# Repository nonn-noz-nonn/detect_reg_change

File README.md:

# 変動する抵抗値の観測

## 概要

- 対象のArduino : Arduino Uno Rev3
- 対象の抵抗値 : 0ohm - 500kohm
    - 電圧変換した抵抗値を0-1023 (10bit) の値として取得します．
- kohmオーダの抵抗値であれば±20dB程度の変動は取得できます．
    - ※ 取得した値の絶対値と精度は考慮していません．
- 下記の項目をシリアルターミナル上で設定できます．
    - 取得する値の下限
    - 取得する値の上限
    - LED点灯の閾値
    - LED点灯の論理
    - 1次LPFの係数
    - 取得間隔(目安)

※ 設定値の範囲や設定方法はArduinoスケッチをご覧ください．

## ソフトウェアのバージョン

作成に用いたソフトウェアのバージョンは次の通りです．

| ソフト名 | バージョン |
| ---- | ---- |
| Arduino IDE | 1.8.19 |
| KiCad | 6.0.2 |

## 注意

本リポジトリのコンテンツ (回路図，BOM，KiCad関連ファイル，Arduinoスケッチ) を流用，応用することは自由ですが，流用・応用した結果生じた問題・障害・損害について，作者 (nonn_noz_nonn (nonn-noz-nonn) ) は一切の責任を負いません．

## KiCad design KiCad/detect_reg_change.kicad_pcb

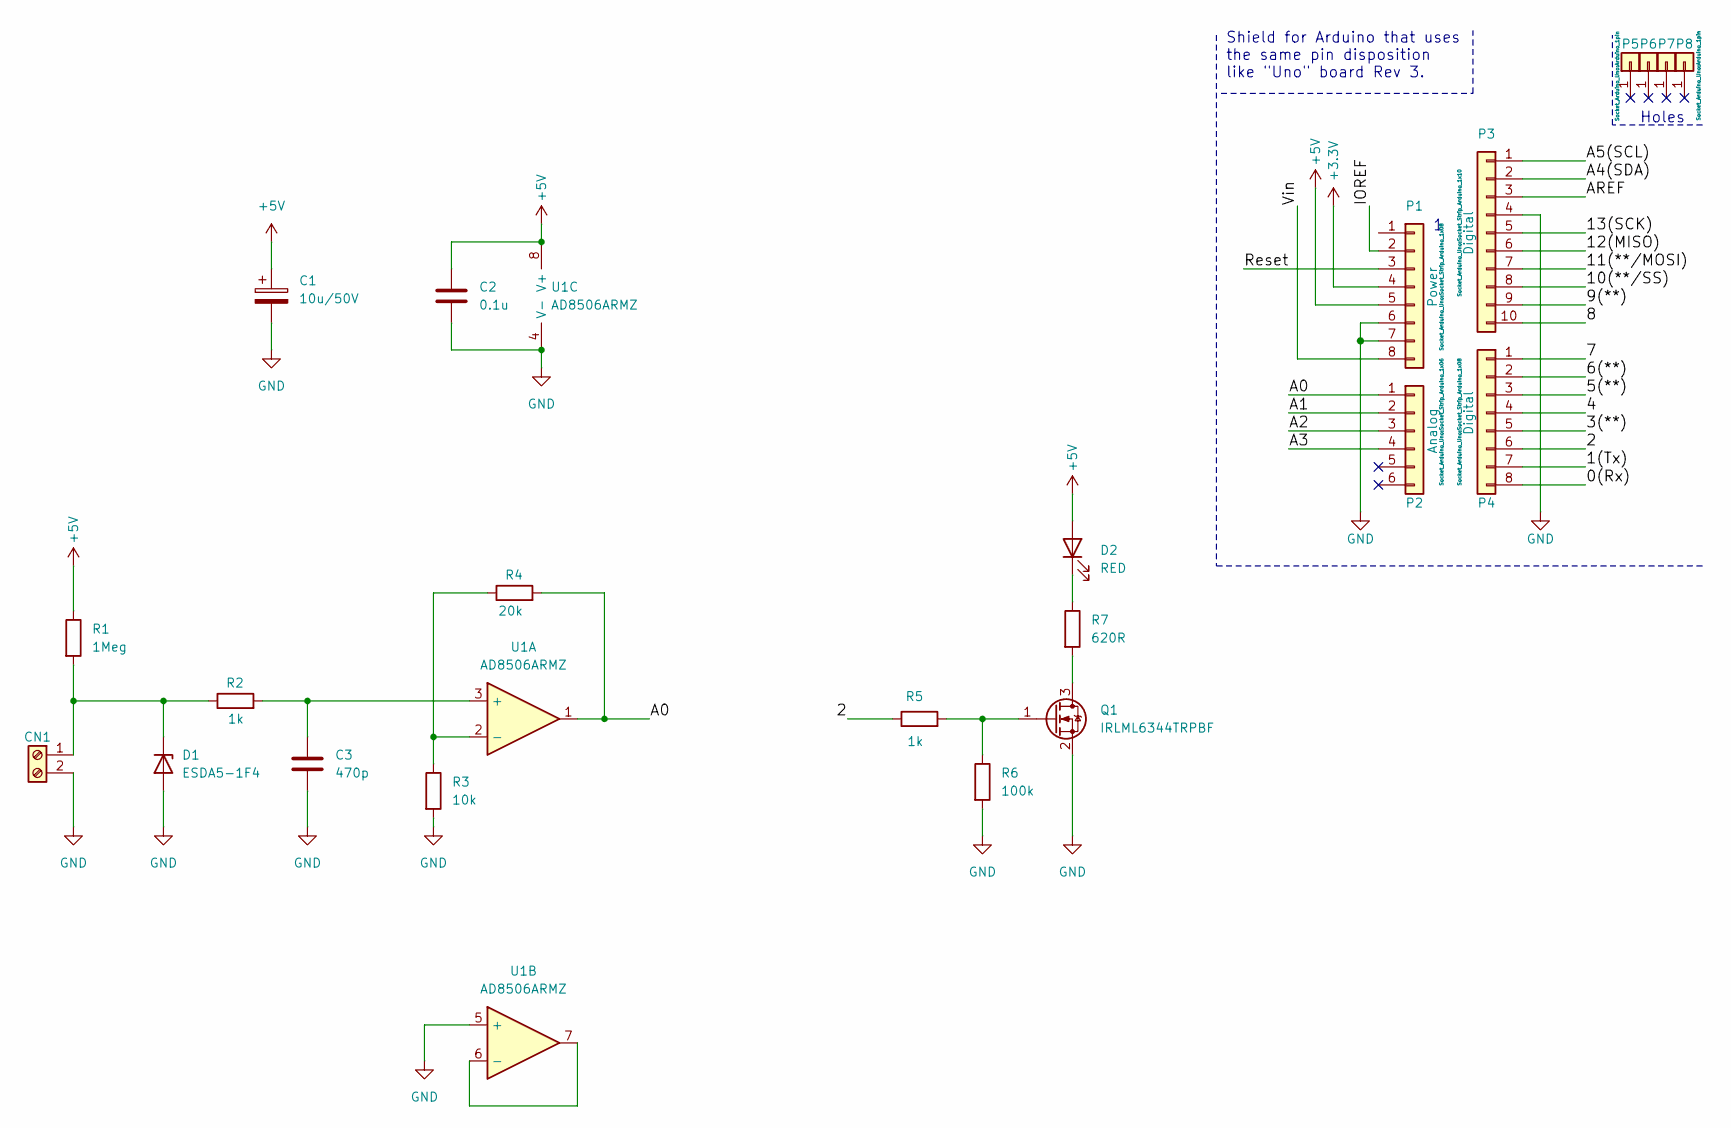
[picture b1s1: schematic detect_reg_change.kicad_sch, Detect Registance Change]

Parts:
C1: 10u/50V; CP_Elec_5x5.4
C2: 0.1u; C_0603_1608Metric
C3: 470p; C_0603_1608Metric
CN1: Screw_Terminal_01x02; PinSocket_1x02_P2.54mm_Vertical
D1: ESDA5-1F4; D_0201_0603Metric
D2: RED; LED_0603_1608Metric
P1: Power; Socket_Strip_Arduino_1x08
P2: Analog; Socket_Strip_Arduino_1x06
P3: Digital; Socket_Strip_Arduino_1x10
P4: Digital; Socket_Strip_Arduino_1x08
P5, P6, P7, P8: CONN_01X01; Arduino_1pin
Q1: IRLML6344TRPBF; SOT-23
R1: 1Meg; R_0603_1608Metric
R2, R5: 1k; R_0603_1608Metric
R3: 10k; R_0603_1608Metric
R4: 20k; R_0603_1608Metric
R6: 100k; R_0603_1608Metric
R7: 620R; R_0603_1608Metric
U1: AD8506ARMZ; TSSOP-8_3x3mm_P0.65mm

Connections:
+3V3: P1.4
+5V: C1.1, C2.1, D2.2 (A), P1.5, R1.1, U1.8 (V+)
/0(Rx): P4.8
/1(Tx): P4.7
/2: P4.6, R5.1
/3(**): P4.5
/4: P4.4
/5(**): P4.3
/6(**): P4.2
/7: P4.1
/8: P3.10
/9(**): P3.9
/10(**/SS): P3.8
/11(**/MOSI): P3.7
/12(MISO): P3.6
/13(SCK): P3.5
/A0: P2.1, R4.2, U1.1
/A1: P2.2
/A2: P2.3
/A3: P2.4
/A4(SDA): P3.2
/A5(SCL): P3.1
/AREF: P3.3
/IOREF: P1.2
/Reset: P1.3
/Vin: P1.8
GND: C1.2, C2.2, C3.2, CN1.2, D1.2 (A), P1.6, P1.7, P3.4, Q1.2 (S), R3.2, R6.2, U1.4 (V-), U1.5 (+)
unnamed: C3.1, R2.2, U1.3 (+)
unnamed: CN1.1, D1.1 (K), R1.2, R2.1
unnamed: D2.1 (K), R7.1
unnamed: Q1.1 (G), R5.2, R6.1
unnamed: Q1.3 (D), R7.2
unnamed: R3.1, R4.1, U1.2 (-)
unnamed: U1.6 (-), U1.7

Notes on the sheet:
Holes
Shield for Arduino that uses the same pin disposition like "Uno" board Rev 3.

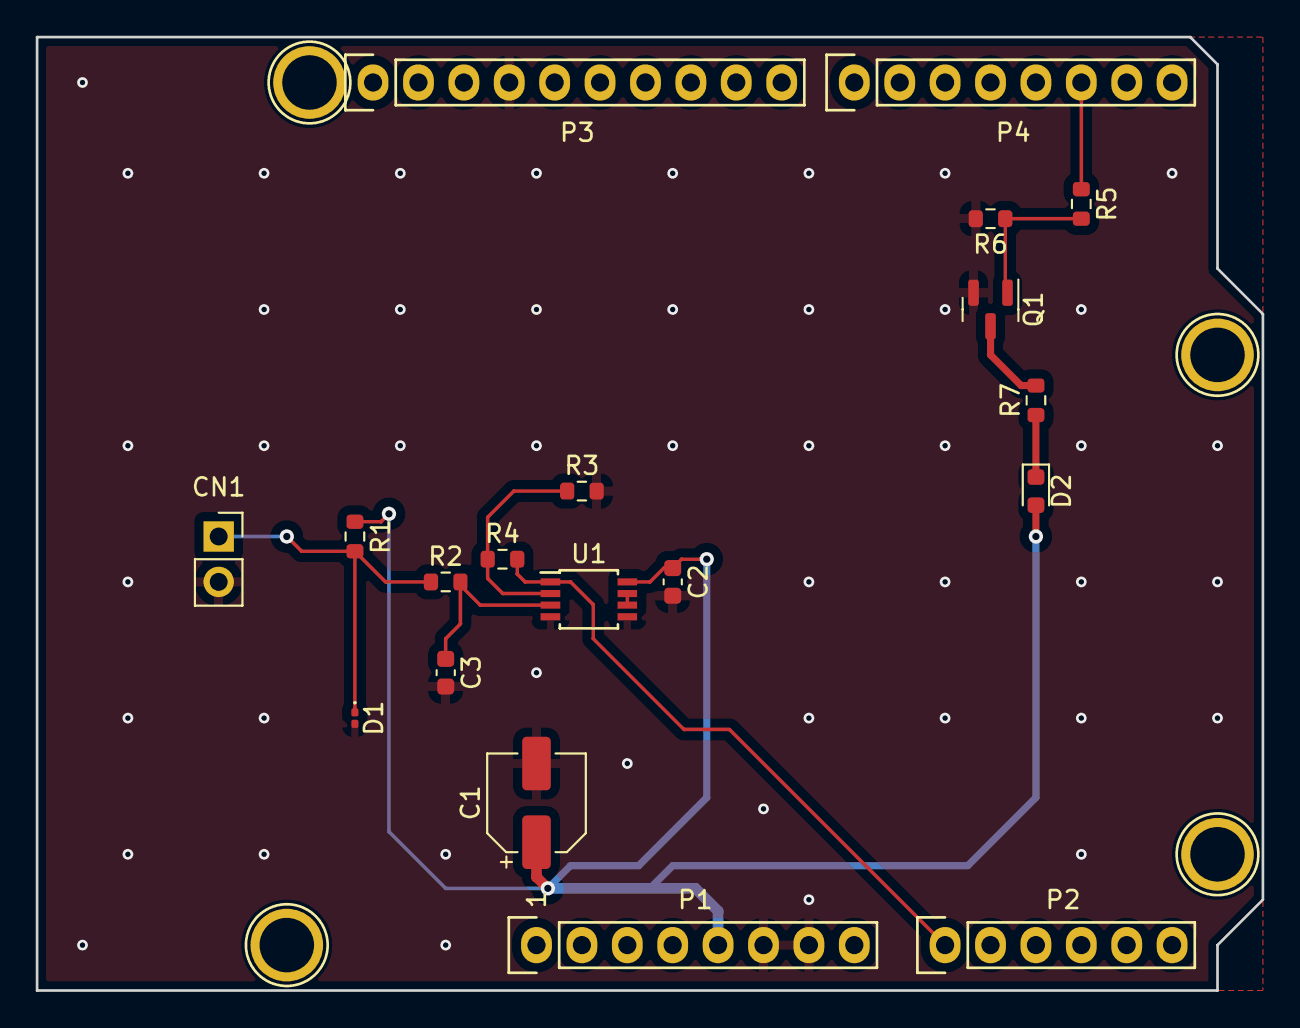
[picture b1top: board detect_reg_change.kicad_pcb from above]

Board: 2 copper layers, 68.6 x 53.3 mm, 23 parts (0 on the bottom side), 11 nets.

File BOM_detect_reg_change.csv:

No.,Reference,Part number,Characteristic,Manufacturer,Description,Qty.
1,C1,865080642006,CAN - SMD,Würth Elektronik,CAP ALUM 10UF 20% 50V SMD,1,https://www.digikey.jp/ja/products/detail/w%C3%BCrth-elektro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
2,C2,C1608X7R1H104K080AA,0603 (1608 Metric),TDK Corporation,CAP CER 0.1UF 50V X7R 0603,1,https://www.digikey.jp/ja/products/detail/tdk-corporation/C1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
3,C3,C1608C0G1H471J080AA,0603 (1608 Metric),TDK Corporation,CAP CER 470PF 50V C0G 0603,1,https://www.digikey.jp/ja/products/detail/tdk-corporation/C1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
4,R1,SG73P1JTTD1004F,0603 (1608 Metric),KOA Speer Electronics,RES 1M OHM 1% 1/3W 0603,1,https://www.digikey.jp/ja/products/detail/koa-speer-electron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
5,R2 R5,SG73P1JTTD1001F,0603 (1608 Metric),KOA Speer Electronics,RES 1K OHM 1% 1/3W 0603,2,https://www.digikey.jp/ja/products/detail/koa-speer-electron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
6,R3,SG73P1JTTD1002F,0603 (1608 Metric),KOA Speer Electronics,RES 10K OHM 1% 1/3W 0603,1,https://www.digikey.jp/ja/products/detail/koa-speer-electron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
7,R4,SG73P1JTTD2002F,0603 (1608 Metric),KOA Speer Electronics,RES 20K OHM 1% 1/3W 0603,1,https://www.digikey.jp/ja/products/detail/koa-speer-electron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
8,R6,SG73P1JTTD1003F,0603 (1608 Metric),KOA Speer Electronics,RES 100K OHM 1% 1/3W 0603,1,https://www.digikey.jp/ja/products/detail/koa-speer-electron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
9,R7,RK73B1JTTD621J,0603 (1608 Metric),KOA Speer Electronics,RES 620 OHM 5% 1/8W 0603,1,https://www.digikey.jp/ja/products/detail/koa-speer-electron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
10,U1,AD8506ARMZ,8-TSSOP,Analog Devices Inc.,IC CMOS 2 CIRCUIT 8MSOP,1,https://www.digikey.jp/ja/products/detail/analog-devices-inc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
11,Q1,IRLML6344TRPBF,SOT-23-3,Infineon Technologies,MOSFET N-CH 30V 5A MICRO3/SOT23,1,https://www.digikey.jp/ja/products/detail/infineon-technolog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
12,D1,ESDA5-1F4,0201 (0603 Metric),STMicroelectronics,TVS DIODE 5.5VWM 9VC 0201,1,https://www.digikey.jp/ja/products/detail/stmicroelectronics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
13,D2,XZMDK53W-1,0603 (1608 Metric),SunLED,LED RED CLEAR CHIP SMD,1,https://www.digikey.jp/ja/products/detail/sunled/XZMDK53W-1/4745950
14,CN1,691210910002,2.54mm pitch Through-Hole,Würth Elektronik,TERM BLOCK 2P HORIZON 2.54MM PCB,1,https://www.digikey.jp/ja/products/detail/w%C3%BCrth-elektro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
15,P1 P2 P3 P4,85,2.54mm pitch Through-Hole,Adafruit Industries LLC,STACKING HEADER ARDUINO SHIELD,1,https://www.digikey.jp/ja/products/detail/adafruit-industrie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

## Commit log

2024-10-17 describe README.md
    describe all the contents.
2024-10-17 modify README.md
    modify author's name in the contents.
2024-10-17 add schematic file
    add image (pdf) file of schematic.
2024-10-17 add BOM file
    add csv file of BOM.
2024-10-17 add KiCad files
    add all the files about KiCad.
2024-10-17 add Arduino sketch
    add sketch (.ino) file for Arduino Uno.
2024-10-17 modify README.md
    modify new line in the contents.
2024-10-17 modify README.md
    correct the description about setting of parameters.
